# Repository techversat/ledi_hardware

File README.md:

ledi_hardware
=============

PCB schematics for LEDI and other circuitry related materials.
The current PCB is designed with CadSoft Eagle.

The schematics and board layout files are freely available for
anyone to reproduce and use for their own personal projects.

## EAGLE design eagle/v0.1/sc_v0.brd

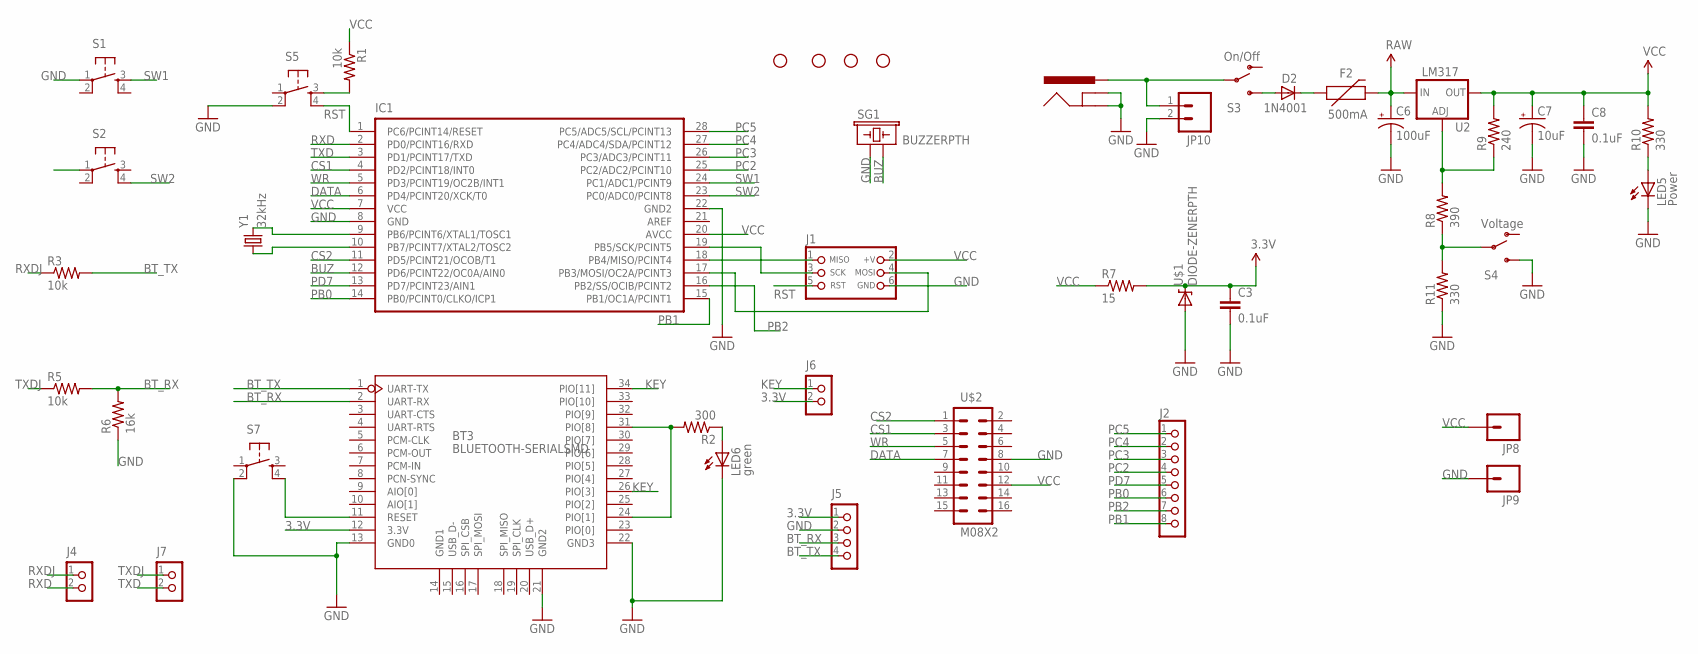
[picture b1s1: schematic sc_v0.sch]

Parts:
BT3: BLUETOOTH-SERIALSMD; SERIAL_BLUETEETH
C3, C8: 0.1uF; CAP-PTH-SMALL2
C6: 100uF; CPOL-RADIAL-100UF-25V
C7: 10uF; CPOL-RADIAL-10UF-25V
D2: 1N4001; DIODE-0.4
F2: 500mA; PTC
IC1: IC_UC_ATMEGA328PDIL; DIL28-N
J1: CON_HEADER_PRG_AVR_ICSP; HEADER_PRG_2X03
J2: CON_HEADER_1X08-PTH; M1X8
J3: POWER_JACKPTH; POWER_JACK_PTH
J4, J6, J7: CON_HEADER_1X02-PTH; M1X2
J5: CON_HEADER_1X04; M1X4
JP1, JP2, JP3, JP4: STAND-OFF
JP8, JP9: M01PTH; 1X01
JP10: M02PTH; 1X02
LED5: Power; LED5MM
LED6: green; LED3MM
R1, R3, R5: 10k; AXIAL-0.3
R2: 300; AXIAL-0.3
R6: 16k; AXIAL-0.3
R7: 15; AXIAL-0.3
R8: 390; AXIAL-0.3
R9: 240; AXIAL-0.3
R10, R11: 330; AXIAL-0.3
S1, S2, S5, S7: TAC_SWITCHPTH; TACTILE-PTH
S3: On/Off; SWITCH-SPST
S4: Voltage; SWITCH-SPST
SG1: BUZZERPTH; BUZZER-12MM
U2: LM317; TO220-ADJ
U$1: DIODE-ZENERPTH; DIODE-ZENER
U$2: M08X2; 2X8
Y1: 32kHz; TC38H

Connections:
3.3V: BT3.12 (3.3V), C3.1, J5.1, J6.2, R7.P$2 (2), U$1.P$1 (C)
BT_RX: BT3.2 (UART-RX), J5.3, R5.P$2 (2), R6.P$2 (2)
BT_TX: BT3.1 (UART-TX), J5.4, R3.P$2 (2)
BUZ: IC1.12 (PD6/PCINT22/OC0A/AIN0), SG1.- (2)
CS1: IC1.4 (PD2/PCINT18/INT0), U$2.3
CS2: IC1.11 (PD5/PCINT21/OCOB/T1), U$2.1
DATA: IC1.6 (PD4/PCINT20/XCK/T0), U$2.7
GND: BT3.13 (GND0), BT3.21 (GND2), BT3.22 (GND3), C3.2, C6.2 (-), C7.2 (-), C8.2, IC1.8 (GND), IC1.22 (GND2), J1.6 (GND), J3.GND, J3.GNDBREAK, J5.2, JP9.1, JP10.2, LED5.K (C), LED6.K (C), R6.P$1 (1), R11.P$1 (1), S1.1, S2.1, S4.3 (S), S5.2, S7.2, SG1.+ (1), U$1.P$2 (A), U$2.8
KEY: BT3.26 (PIO[3]), BT3.34 (PIO[11]), J6.1
unnamed: IC1.9 (PB6/PCINT6/XTAL1/TOSC1), Y1.2
unnamed: IC1.10 (PB7/PCINT7/XTAL2/TOSC2), Y1.1
unnamed: IC1.18 (PB4/MISO/PCINT4), J1.1 (MISO)
unnamed: IC1.19 (PB5/SCK/PCINT5), J1.3 (SCK)
unnamed: IC1.17 (PB3/MOSI/OC2A/PCINT3), J1.4 (MOSI)
unnamed: R8.P$2 (2), R9.P$1 (1), U2.ADJ
unnamed: LED5.A, R10.P$1 (1)
unnamed: BT3.24 (PIO[1]), BT3.31 (PIO[8]), R2.P$2 (2)
unnamed: D2.C, F2.P$1 (1)
unnamed: D2.A, S3.3 (S)
unnamed: J3.PWR, JP10.1, S3.2
unnamed: R8.P$1 (1), R11.P$2 (2), S4.2
unnamed: R1.P$2 (2), S5.3
unnamed: BT3.11 (RESET), S7.4
unnamed: LED6.A, R2.P$1 (1)
PB0: IC1.14 (PB0/PCINT0/CLKO/ICP1), J2.6
PB1: IC1.15 (PB1/OC1A/PCINT1), J2.8
PB2: IC1.16 (PB2/SS/OCIB/PCINT2), J2.7
PC2: IC1.25 (PC2/ADC2/PCINT10), J2.4
PC3: IC1.26 (PC3/ADC3/PCINT11), J2.3
PC4: IC1.27 (PC4/ADC4/SDA/PCINT12), J2.2
PC5: IC1.28 (PC5/ADC5/SCL/PCINT13), J2.1
PD7: IC1.13 (PD7/PCINT23/AIN1), J2.5
RAW: C6.1 (+), F2.P$2 (2), U2.IN
RST: IC1.1 (PC6/PCINT14/RESET), J1.5 (RST), S5.4
RXD: IC1.2 (PD0/PCINT16/RXD), J4.2
RXDJ: J4.1, R3.P$1 (1)
SW1: IC1.24 (PC1/ADC1/PCINT9), S1.3
SW2: IC1.23 (PC0/ADC0/PCINT8), S2.4
TXD: IC1.3 (PD1/PCINT17/TXD), J7.2
TXDJ: J7.1, R5.P$1 (1)
VCC: C7.1 (+), C8.1, IC1.7 (VCC), IC1.20 (AVCC), J1.2 (+V), JP8.1, R1.P$1 (1), R7.P$1 (1), R9.P$2 (2), R10.P$2 (2), U2.OUT, U$2.12
WR: IC1.5 (PD3/PCINT19/OC2B/INT1), U$2.5

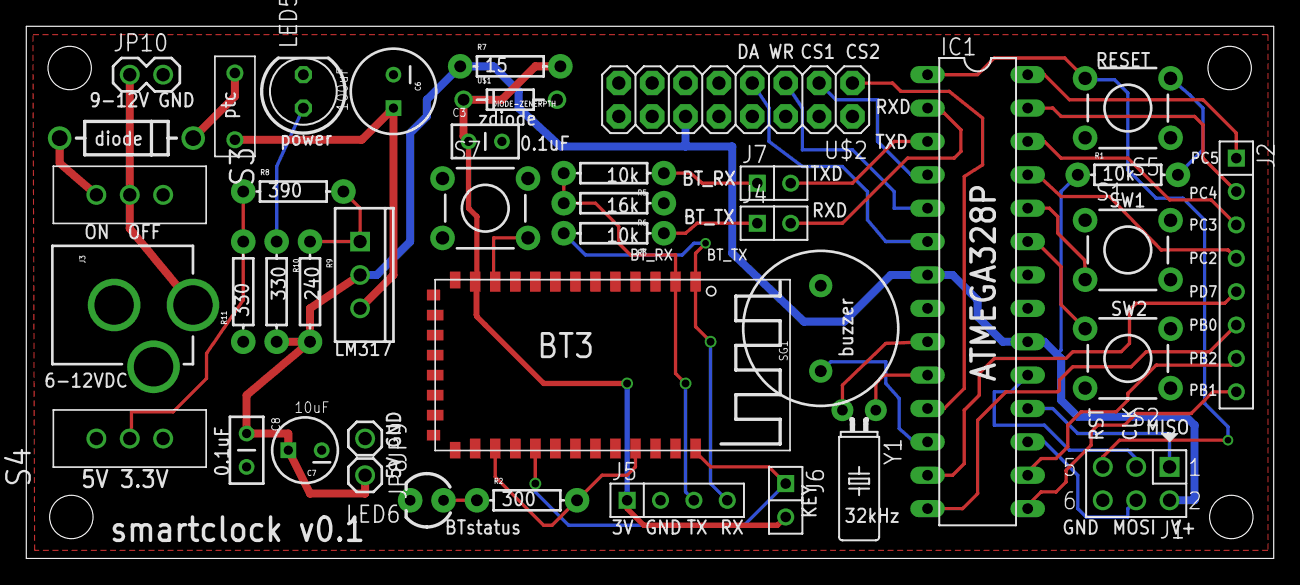
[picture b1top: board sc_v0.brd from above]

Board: 2 copper layers, 94.9 x 40.5 mm, 45 parts (0 on the bottom side), 42 nets.

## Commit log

2012-12-29 test

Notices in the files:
parts and their libraries:
SparkFun: Licensing: CC v3.0 Share-Alike You are welcome to use this library for commercial purposes.
